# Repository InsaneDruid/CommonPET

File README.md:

# The CommonPET
The CommonPET is a 100% compatible replica of the SuperPet combo board for PET/CBM 8032 computers from 1981.
It implements all the features, including the 64K RAM addon, compatibility for the OS9 MMU well as the support for the internal RS-232 connector.

Most of the components are readily available. Chips not available from Mouser or Digikey can still be purchased as NOS from a variety of sources.

[Schematic](https://github.com/InsaneDruid/CommonPET/blob/main/CommonPET.pdf "Schematic")  

[Bill of Materials](https://htmlpreview.github.io/?https://github.com/InsaneDruid/CommonPET/blob/main/bom/CommonPET_bom.html "Bill of Materials")
## The Firmware
The Firmware of the SuperPET is available at zimmers.net: http://www.zimmers.net/anonftp/pub/cbm/firmware/computers/pet/SuperPET/index.html

UA3: characters.901640-01.bin (PETside CharROM):

U47: waterloo-a000-bfff.970018-12.bin

U48: waterloo-c000-dfff.970019-12.bin

U49: waterloo-e000-ffff-970034-12.bin (50Hz Version)

U49: waterloo-e000-ffff.970020-12.bin (60Hz Version)

Adapters to use 2764 EPROM work, 27hc641 that are programmed to be pin compatible to 2364 are recommended.

## The RS232 interface
CBM in its infinite wisdom only provided +5V and -9V for the 1488 line driver. A low voltage 1488E or 14C88 is recommended.

## The OS/9 MMU addon board
A replica of the OS/9 addon board can be found in the [os9_mmu folder](https://github.com/InsaneDruid/CommonPET/blob/main/os9_mmu/ "os9_mmu folder")

## The License
This work is licensed under a Creative Commons Attribution-ShareAlike 4.0 International License.  
See https://creativecommons.org/licenses/by-sa/4.0/.

## The Credits
This work would not have been possible without the help from a bunch of amazing people from [VzEkC e. V. forums](https://forum.classic-computing.de/forum/ "forum.classic-computing.de"). Many thanks go out to:

* *for(;;)* - for creating the amazing µMMF project that inspired this work
* *vossi* - for providing excellent images of a ASSY 324100 board
* *CBM_Ba* and *Richi*- for building and testing the first prototype

Special credits go out to *Mike Naberezny* for researching the OS/9 MMU schematics

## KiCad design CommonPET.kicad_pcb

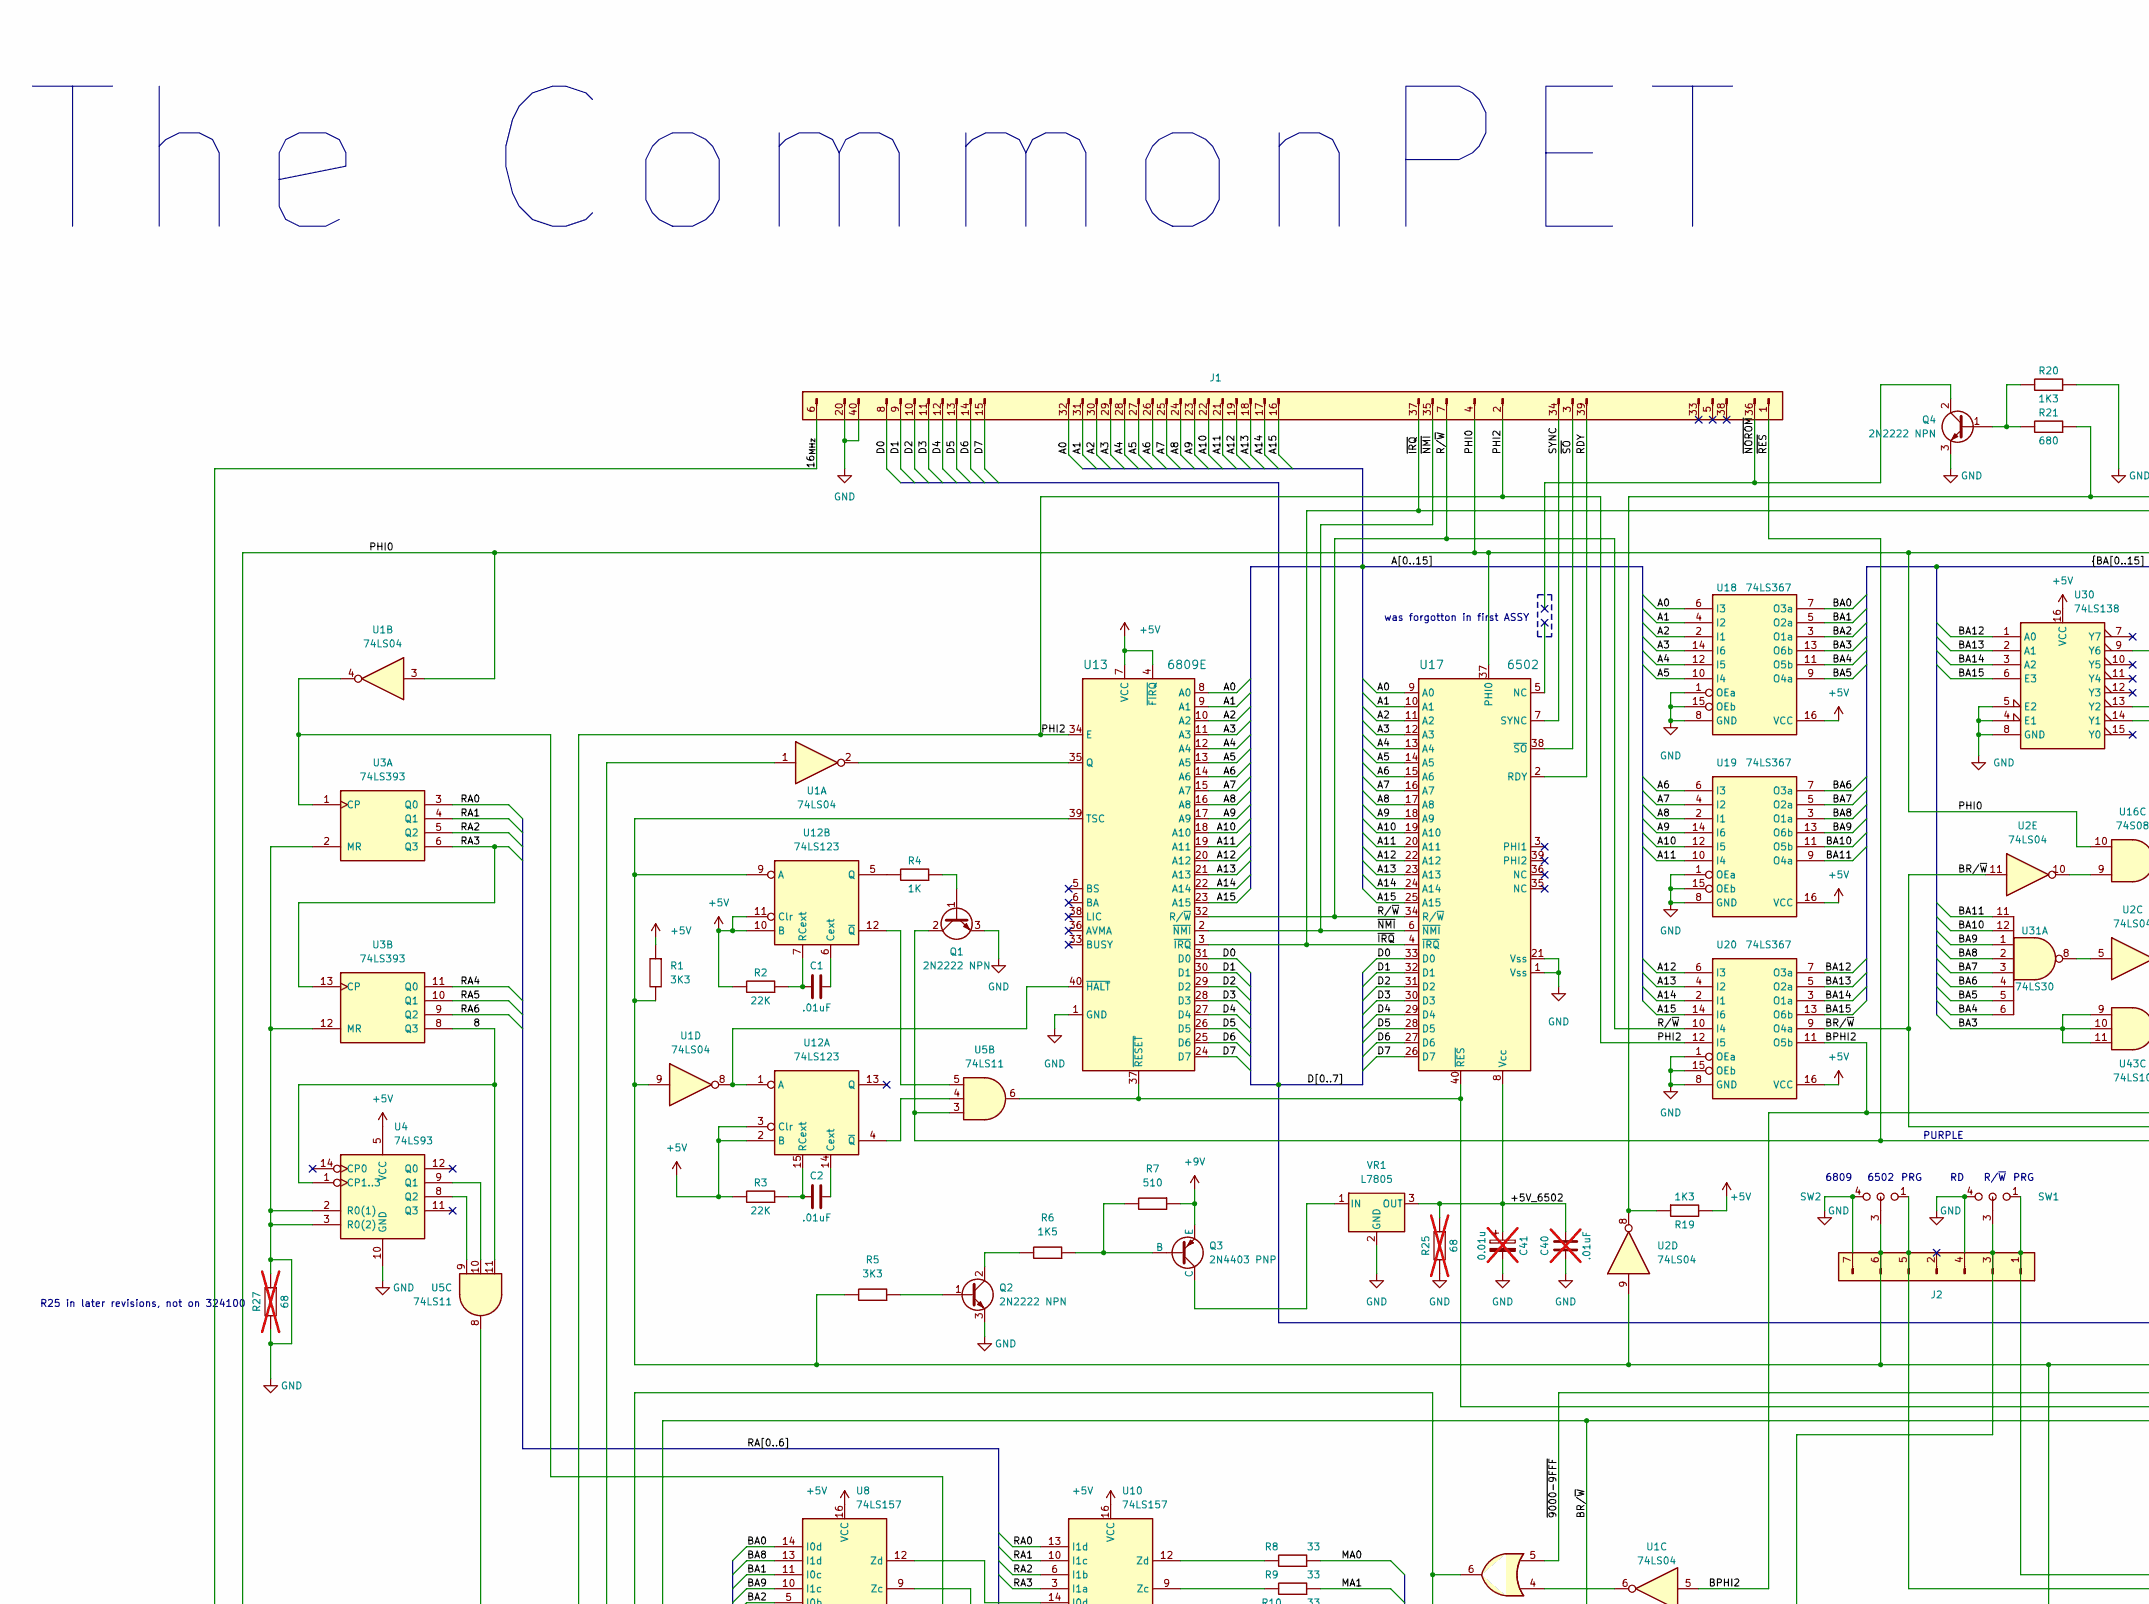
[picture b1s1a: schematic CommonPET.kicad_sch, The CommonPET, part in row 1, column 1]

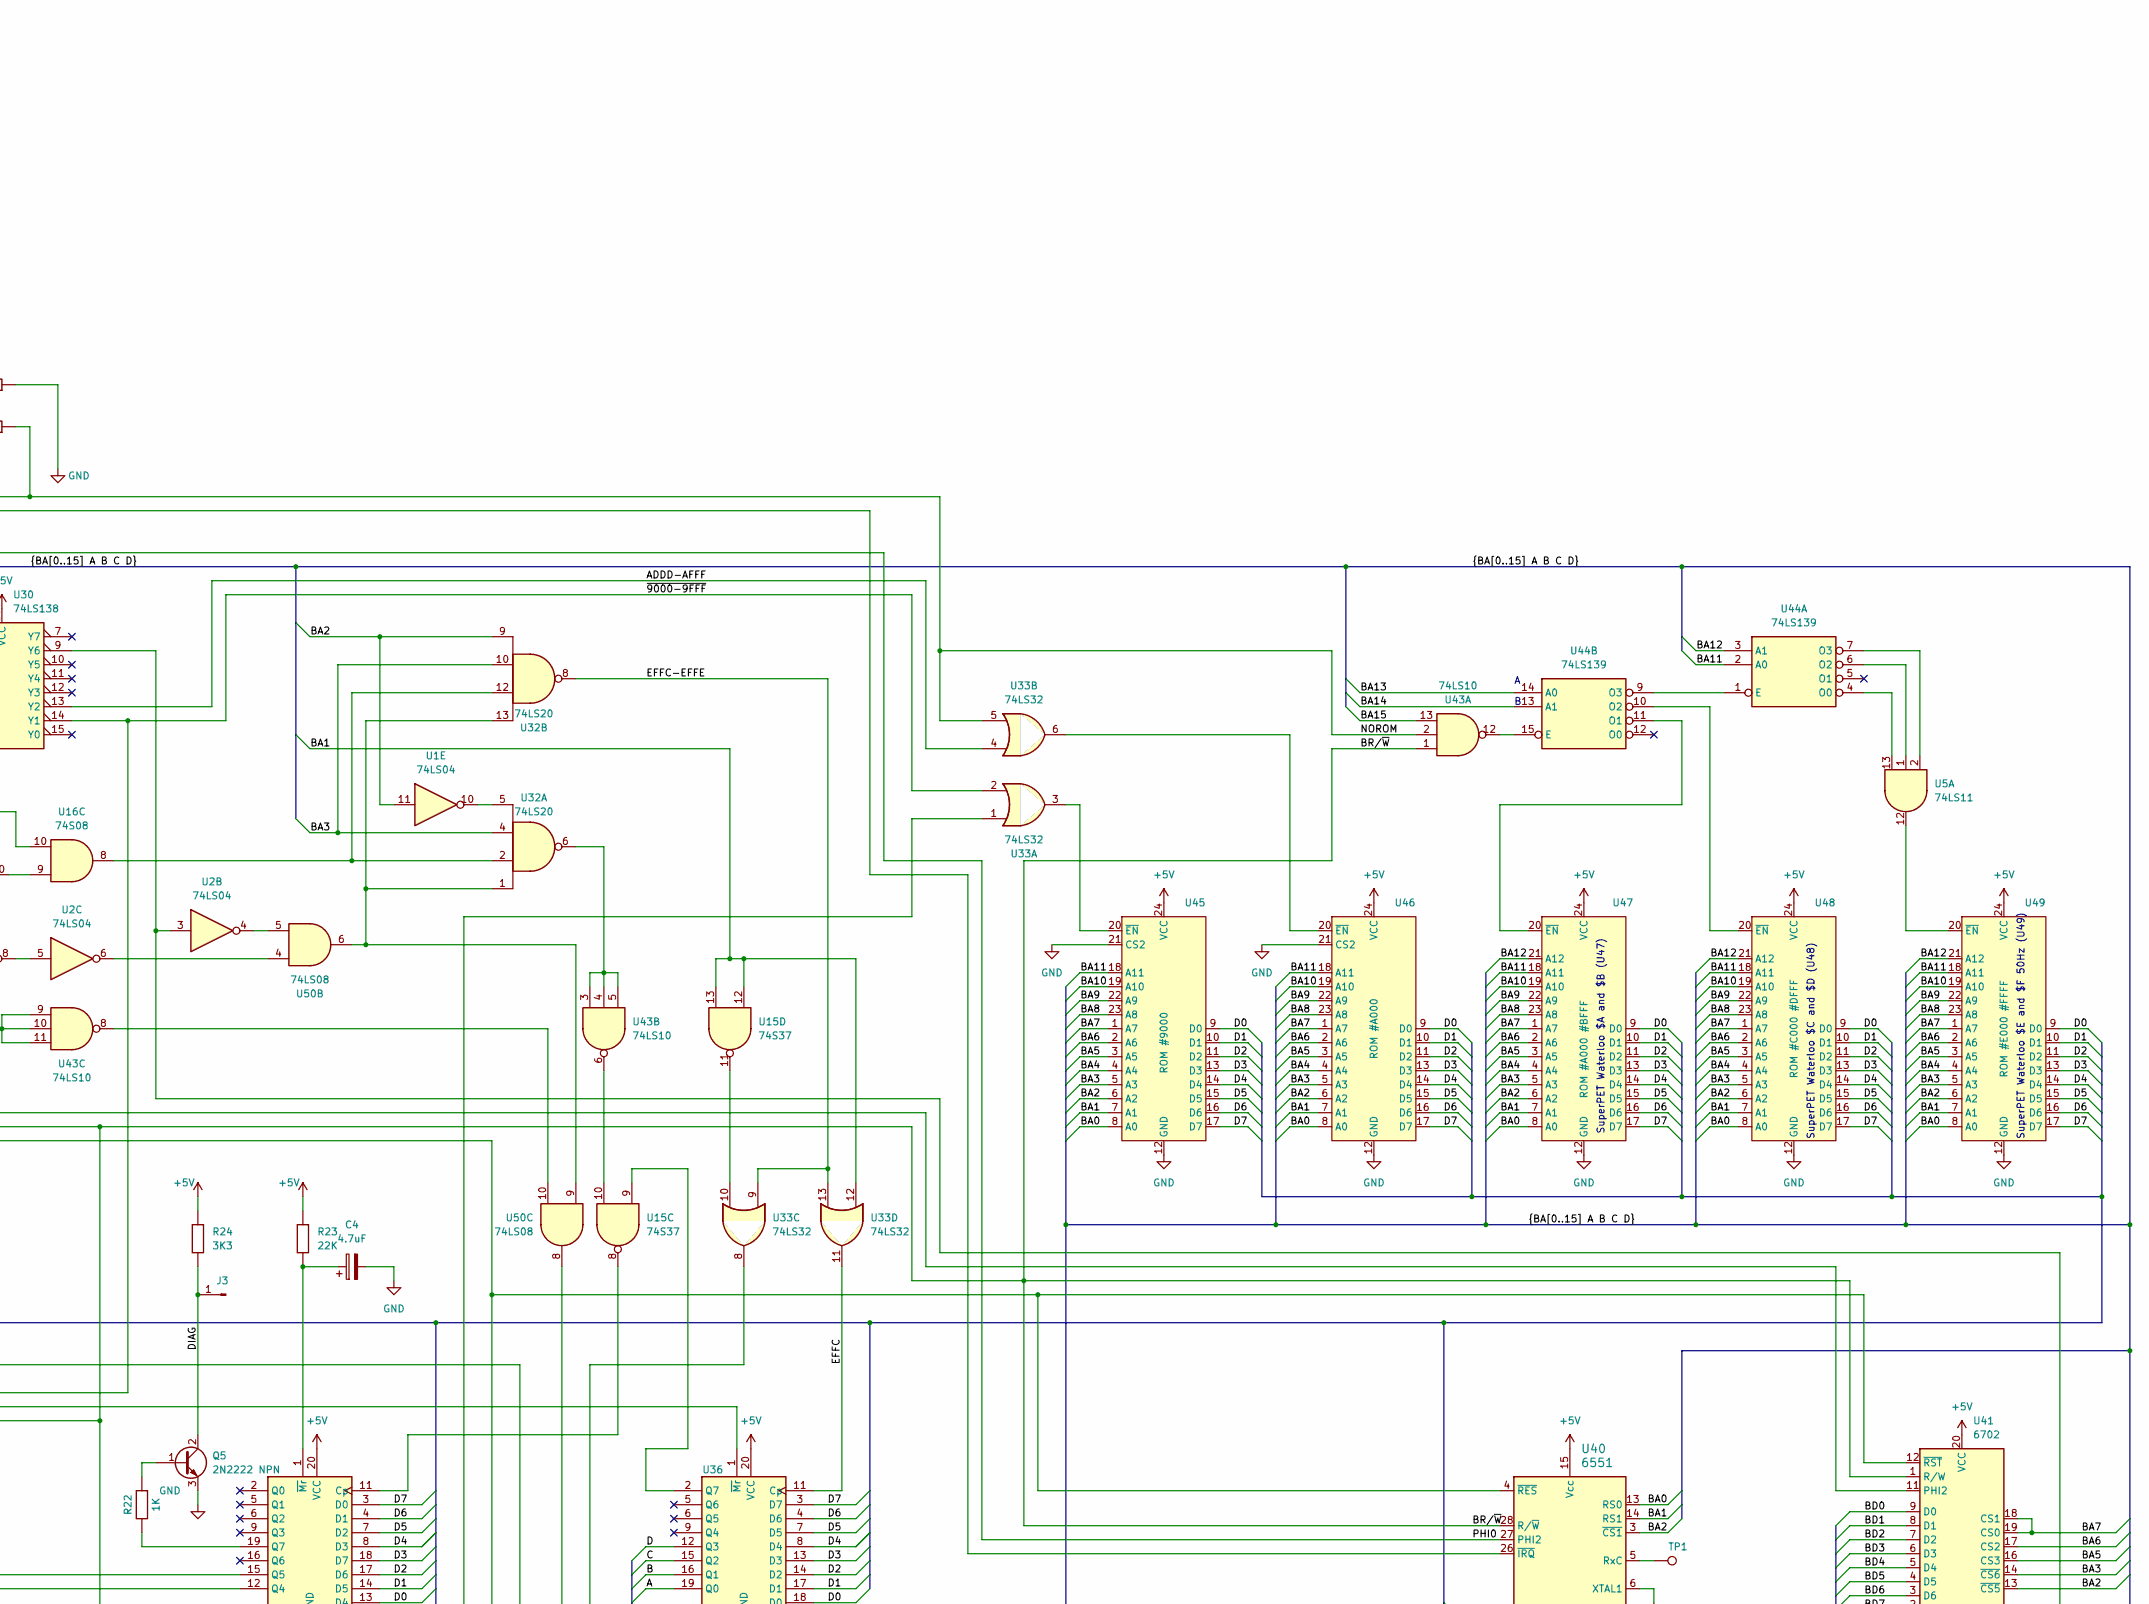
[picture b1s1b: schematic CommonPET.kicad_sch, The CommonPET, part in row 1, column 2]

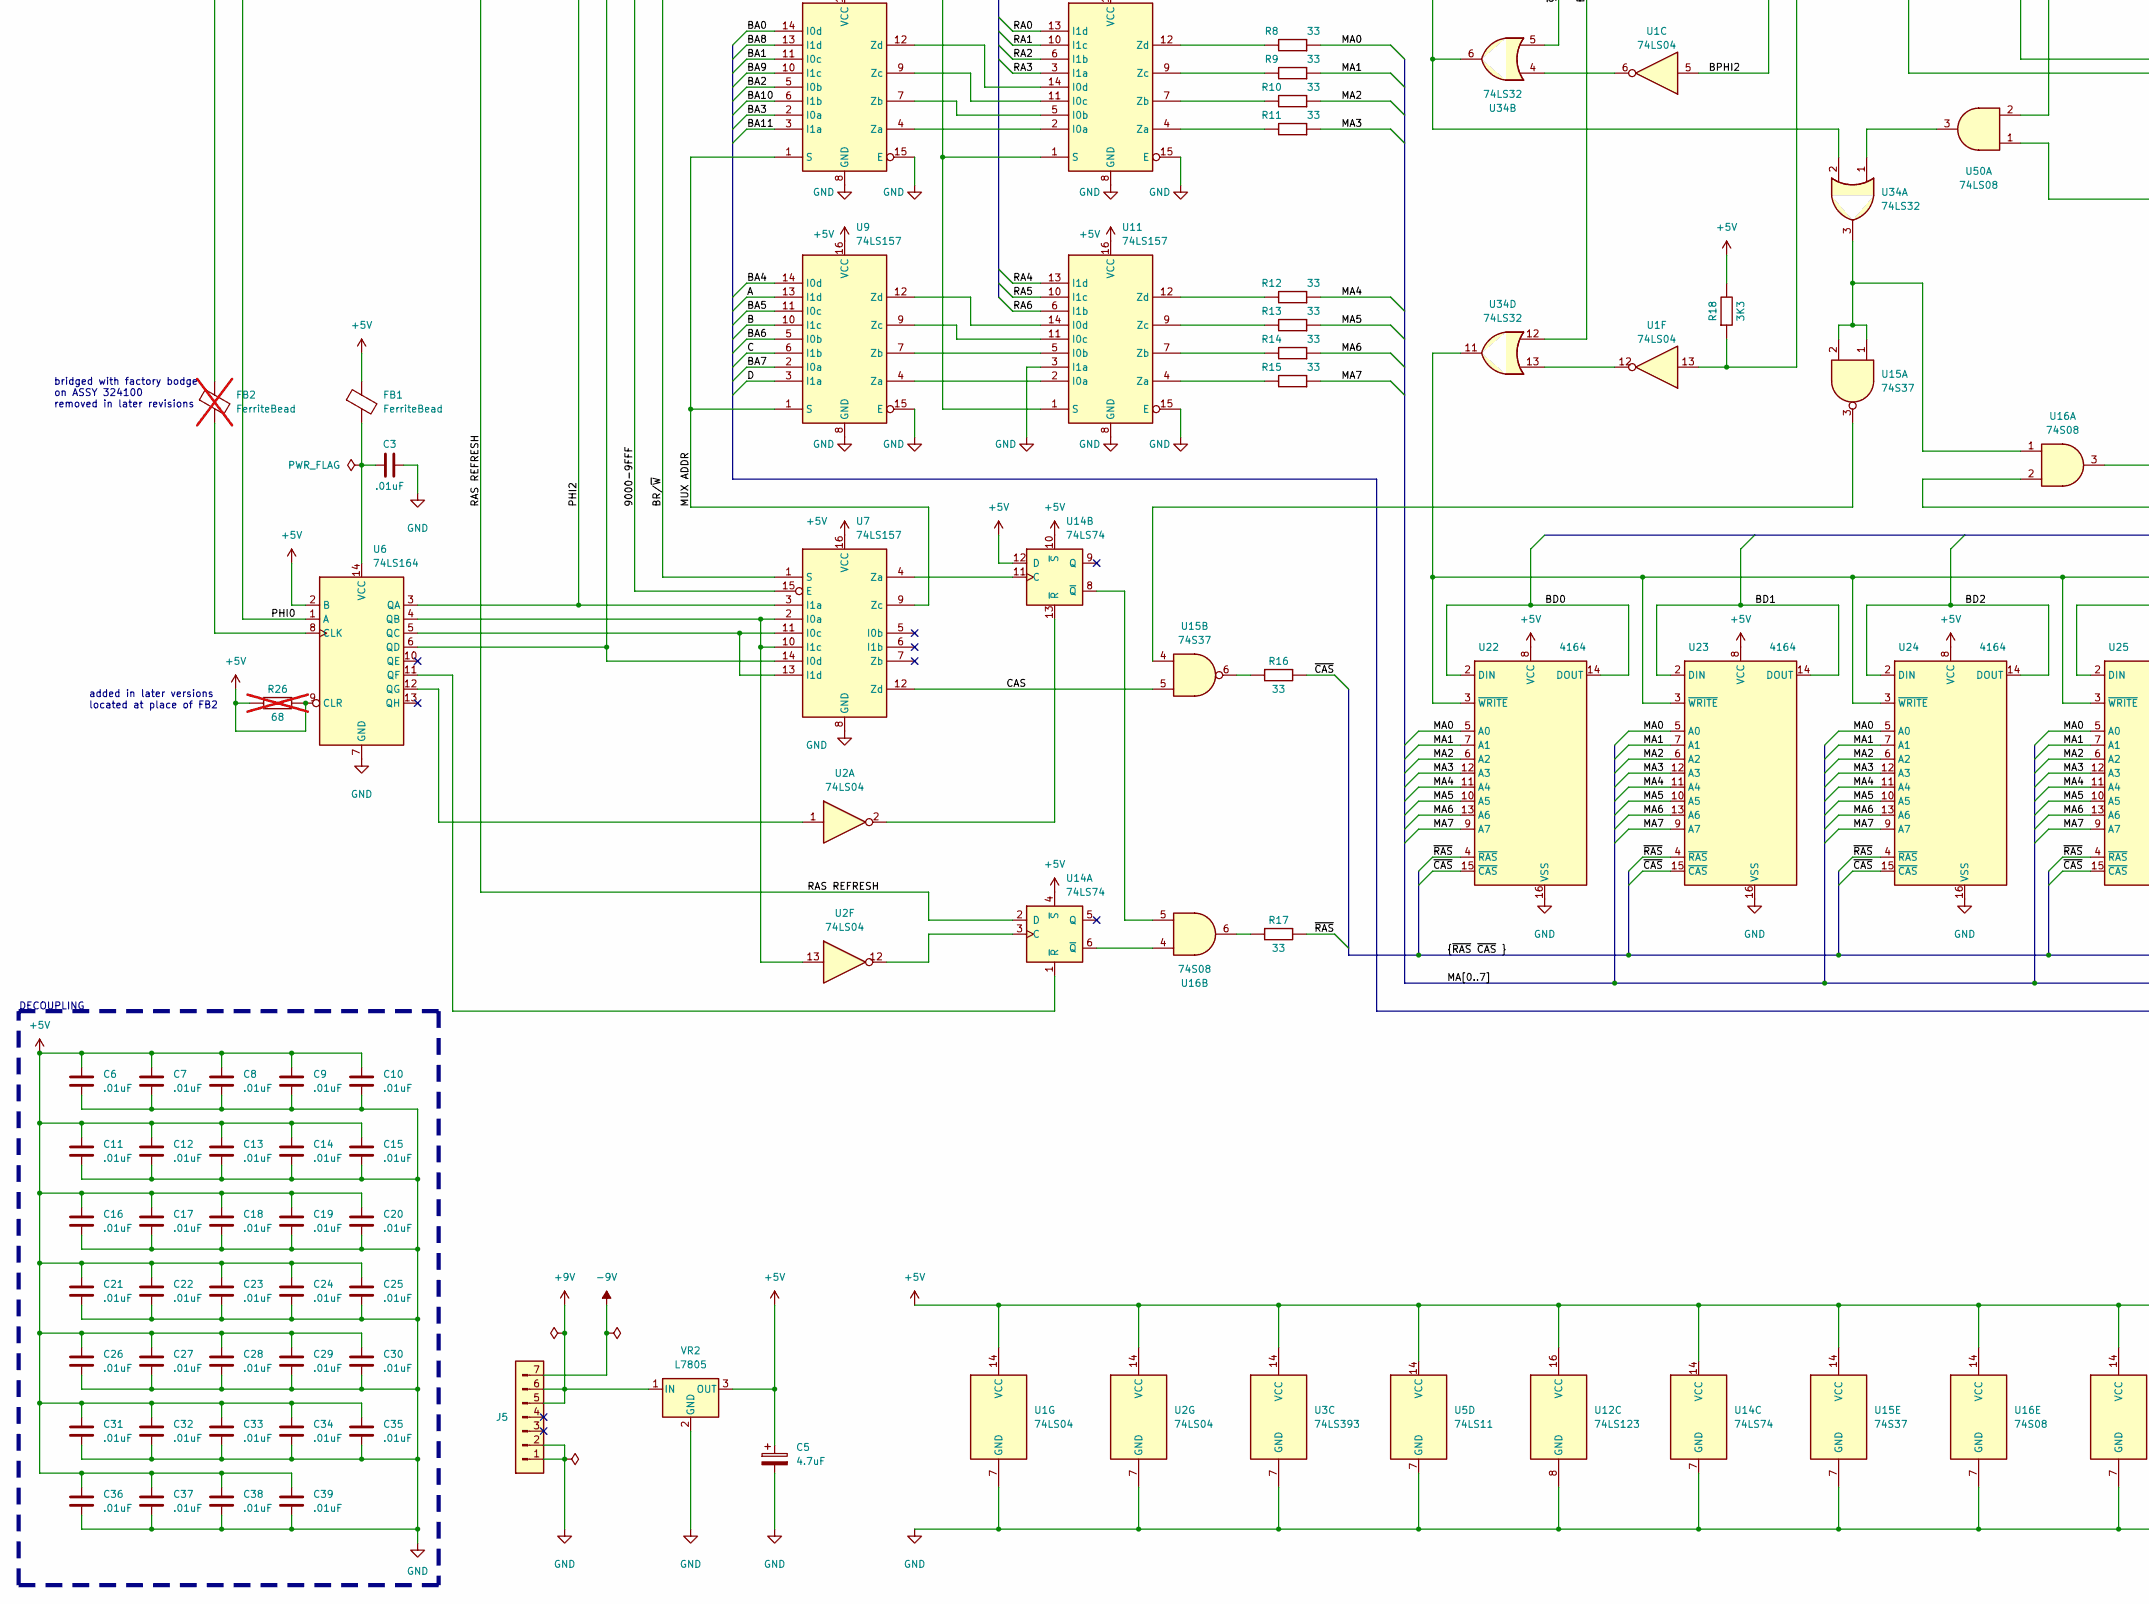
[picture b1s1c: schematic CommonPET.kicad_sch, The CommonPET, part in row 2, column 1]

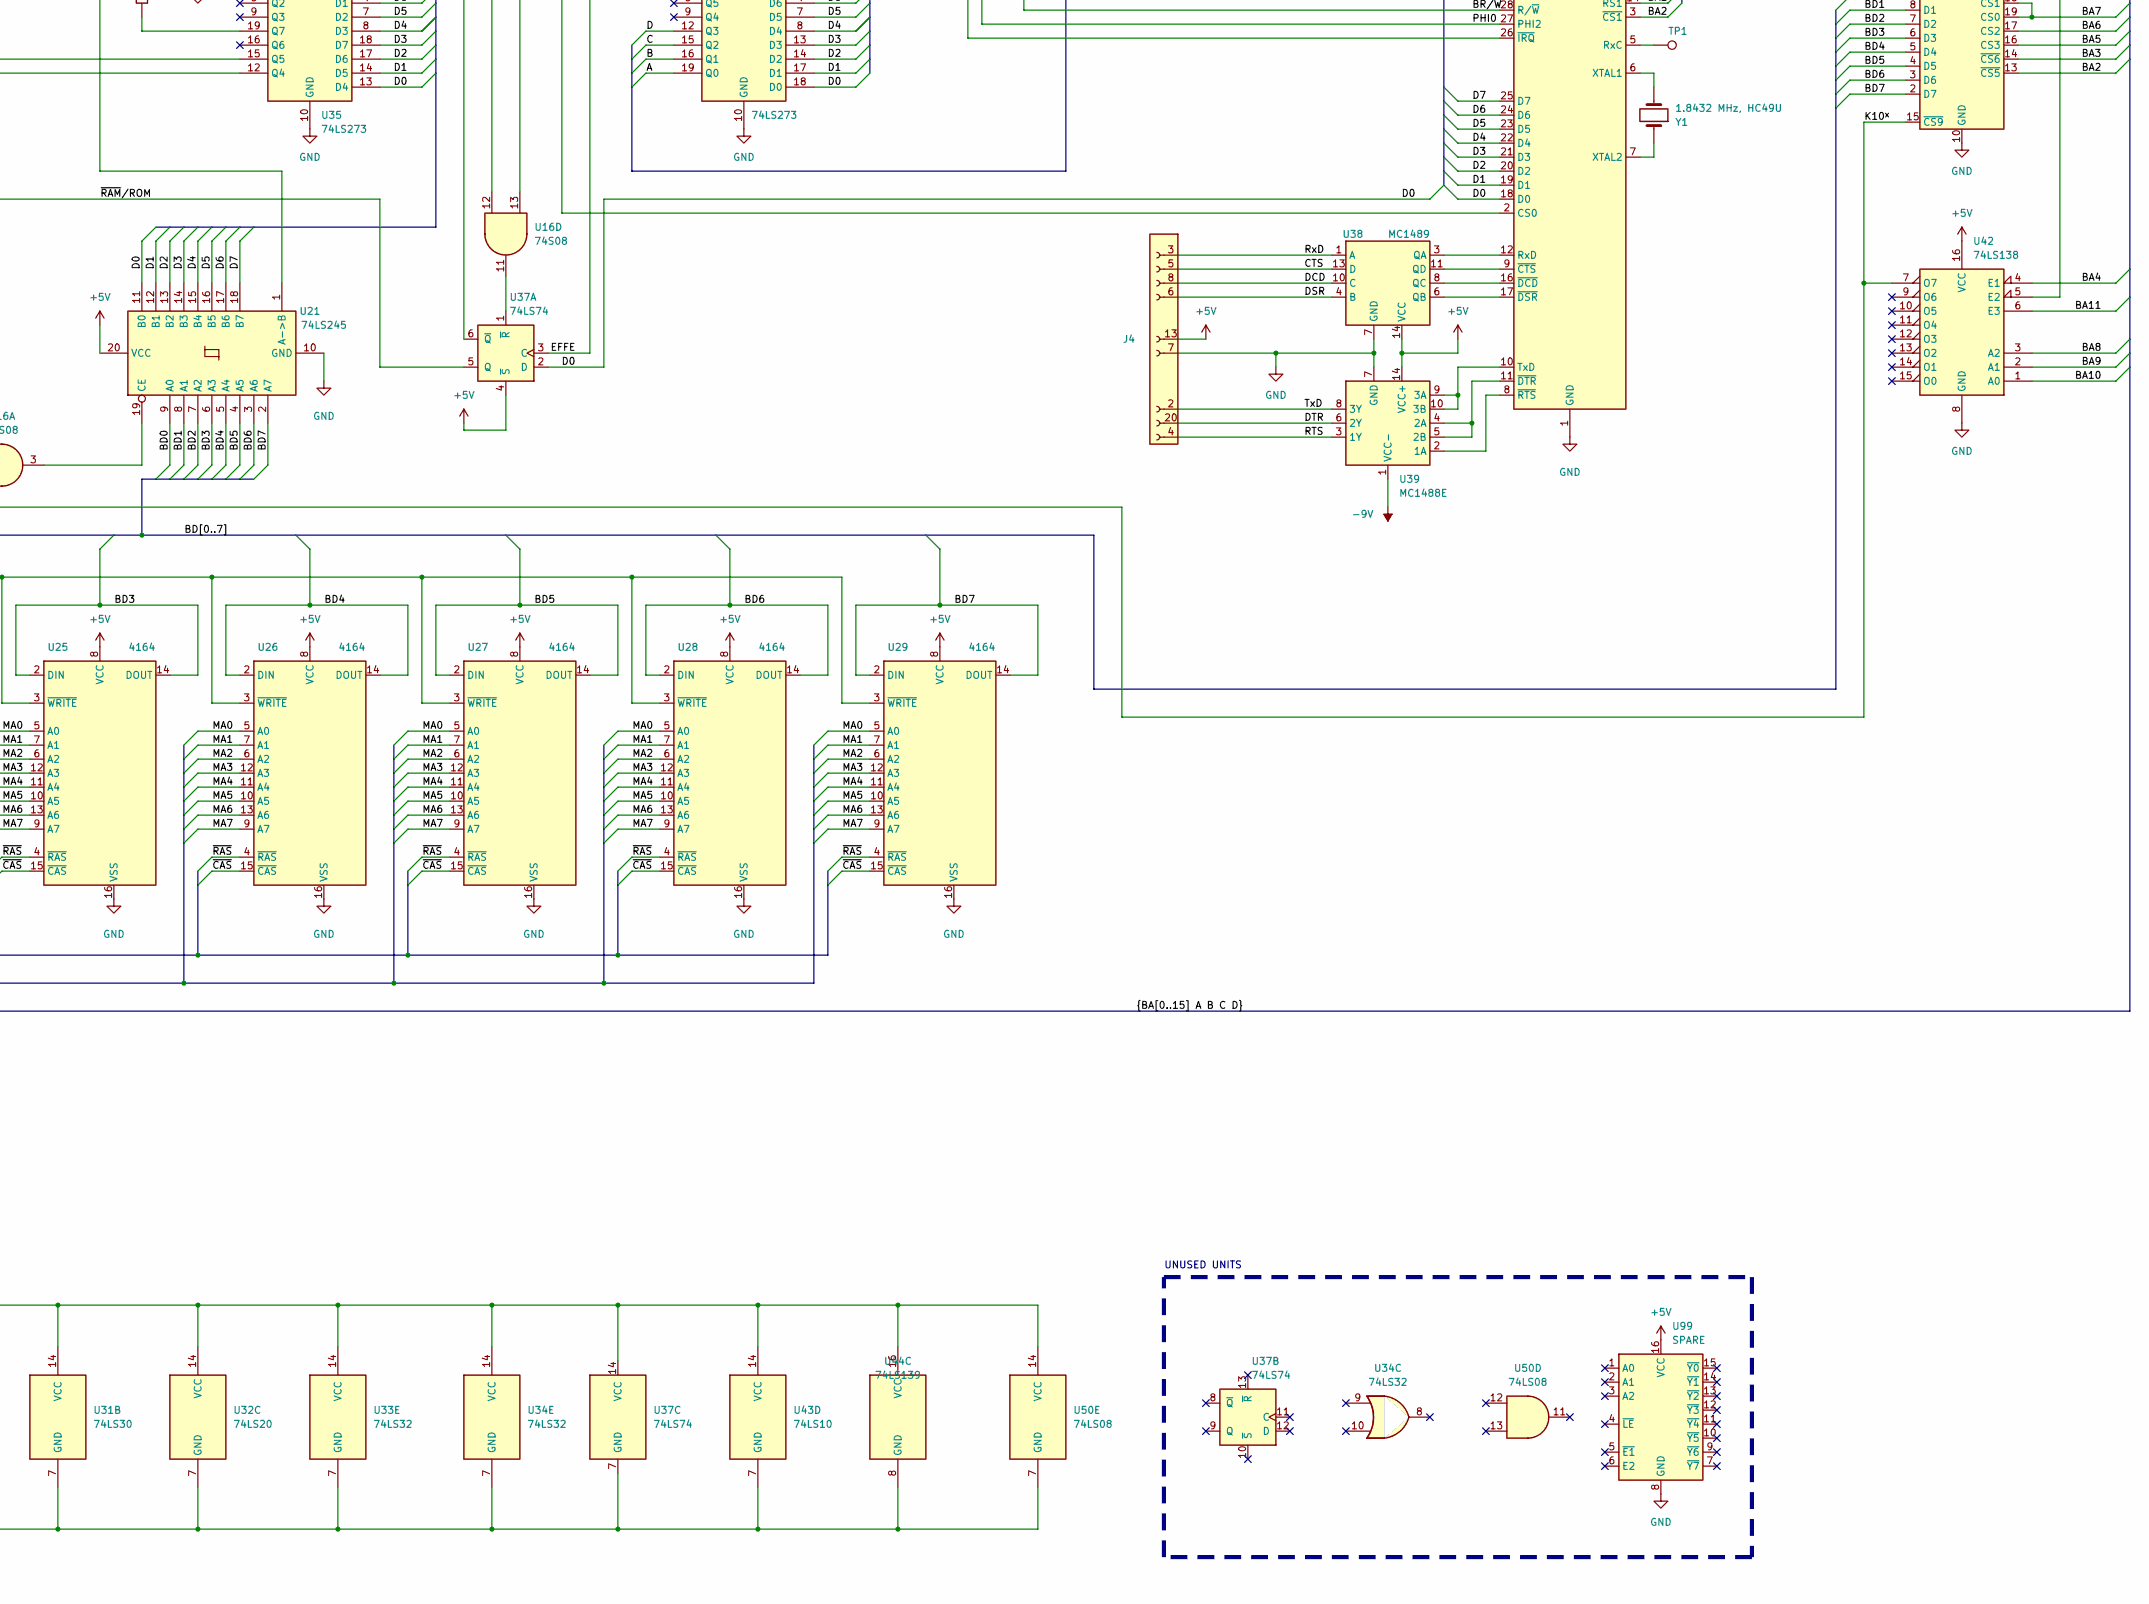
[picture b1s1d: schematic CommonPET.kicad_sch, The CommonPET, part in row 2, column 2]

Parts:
C1, C2, C3, C6, C7, C8, C9, C10, C11, C12, C13, C14, C15, C16, C17, C18, C19, C20, C21, C22, C23, C24, C25, C26, C27, C28, C29, C30, C31, C32, C33, C34, C35, C36, C37, C38, C39: .01uF; C_Axial_L3.8mm_D2.6mm_P12.54mm_Horizontal
C4, C5: 4.7uF; CP_Axial_L11.0mm_D6.0mm_P20.32mm
C40: .01uF; C_Axial_L3.8mm_D2.6mm_P12.54mm_Horizontal_notpopulated; not fitted
C41: 0.01u; CP_Axial_L11.0mm_D6.0mm_P20.32mm_notpopulated; not fitted
FB1: FerriteBead; C_Axial_L3.8mm_D2.6mm_P12.54mm_Horizontal
FB2: FerriteBead; C_Axial_L3.8mm_D2.6mm_P12.54mm_Horizontal; not fitted
J1: Conn_01x40_Pin; PinHeader_2x20_P2.54mm_Vertical
J2, J5: Conn_01x07_Pin; PinHeader_1x07_P2.54mm_Vertical
J3: Conn_01x01_Pin; PinHeader_1x01_P2.54mm_Vertical
J4: Conn_01x25_Socket; DSUB-25_Female_Horizontal_P2.77x2.84mm_EdgePinOffset9.90mm_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
Q1, Q2, Q4, Q5: 2N2222 NPN; TO-18-3
Q3: 2N4403 PNP; TO-92
R1, R5, R18, R24: 3K3; R_Axial_DIN0207_L6.3mm_D2.5mm_P15.24mm_Horizontal
R2, R3, R23: 22K; R_Axial_DIN0207_L6.3mm_D2.5mm_P15.24mm_Horizontal
R4, R22: 1K; R_Axial_DIN0207_L6.3mm_D2.5mm_P15.24mm_Horizontal
R6: 1K5; R_Axial_DIN0207_L6.3mm_D2.5mm_P15.24mm_Horizontal
R7: 510; R_Axial_DIN0207_L6.3mm_D2.5mm_P15.24mm_Horizontal
R8, R9, R10, R11, R12, R13, R14, R15, R16, R17: 33; R_Axial_DIN0207_L6.3mm_D2.5mm_P15.24mm_Horizontal
R19, R20: 1K3; R_Axial_DIN0207_L6.3mm_D2.5mm_P15.24mm_Horizontal
R21: 680; R_Axial_DIN0207_L6.3mm_D2.5mm_P15.24mm_Horizontal
R25: 68; R_Axial_DIN0207_L6.3mm_D2.5mm_P15.24mm_Horizontal__notpopul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; not fitted
R26, R27: 68; R_Axial_DIN0207_L6.3mm_D2.5mm_P15.24mm_Horizontal; not fitted
SW1, SW2: SW_DP3T
TP1: TestPoint; TestPoint_THTPad_1.0x1.0mm_Drill0.5mm
U1, U2: 74LS04; DIP-14_W7.62mm
U3: 74LS393; DIP-14_W7.62mm
U4: 74LS93; DIP-14_W7.62mm
U5: 74LS11; DIP-14_W7.62mm
U6: 74LS164; DIP-14_W7.62mm
U7, U8, U9, U10, U11: 74LS157; DIP-16_W7.62mm
U12: 74LS123; DIP-16_W7.62mm
U13: 6809E; DIP-40_W15.24mm_socket
U14, U37: 74LS74; DIP-14_W7.62mm
U15: 74S37; DIP-14_W7.62mm
U16: 74S08; DIP-14_W7.62mm
U17: 6502; DIP-40_W15.24mm_socket
U18, U19, U20: 74LS367; DIP-16_W7.62mm
U21: 74LS245; DIP-20_W7.62mm
U22, U23, U24, U25, U26, U27, U28, U29: 4164; DIP-16_W7.62mm
U30, U42: 74LS138; DIP-16_W7.62mm
U31: 74LS30; DIP-14_W7.62mm
U32: 74LS20; DIP-14_W7.62mm
U33, U34: 74LS32; DIP-14_W7.62mm
U35, U36: 74LS273; DIP-20_W7.62mm
U38: MC1489; DIP-14_W7.62mm
U39: MC1488E; DIP-14_W7.62mm
U40: 6551; DIP-28_W15.24mm
U41: 6702; DIP-20_W7.62mm
U43: 74LS10; DIP-14_W7.62mm
U44: 74LS139; DIP-16_W7.62mm
U45: ROM #9000; DIP-24_W15.24mm_socket
U46: ROM #A000; DIP-24_W15.24mm_socket
U47: ROM #A000 #BFFF; DIP-24_W15.24mm
U48: ROM #C000 #DFFF; DIP-24_W15.24mm
U49: ROM #E000 #FFFF; DIP-24_W15.24mm
U50: 74LS08; DIP-14_W7.62mm
U99: SPARE; SPARE_DIP-16_W7.62mm
VR1: L7805; TO-220-3_Horizontal_TabDown
VR2: L7805; TO-220-3_Horizontal_TabDown_HeatSinked
Y1: 1.8432 MHz, HC49U; Crystal_HC33-U_Horizontal

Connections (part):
+5V: C5.1, C6.1, C7.1, C8.1, C9.1, C10.1, C11.1, C12.2, C13.2, C14.1, C15.1, C16.1, C17.1, C18.1, C19.1, C20.1, C21.1, C22.1, C23.1, C24.1, C25.1, C26.1, C27.1, C28.1, C29.1, C30.1, C31.1, C32.1, C33.1, C34.1, C35.1, C36.1, C37.1, C38.1, C39.1, FB1.1, J4.13 (Pin_7), R1.2, R2.1, R3.1, R18.1, R19.1, R23.2, R24.2, U1.14 (VCC), U2.14 (VCC), U3.14 (VCC), U4.5 (VCC), U5.14 (VCC), U6.2 (B), U6.9 (CLR), U7.16 (VCC), U8.16 (VCC), U9.16 (VCC), U10.16 (VCC), U11.16 (VCC), U12.2 (B), U12.3 (Clr), U12.10 (B), U12.11 (Clr), U12.16 (VCC), U13.4 (~FIRQ), U13.7 (VCC), U14.4 (~S), U14.10 (~S), U14.12 (D), U14.14 (VCC), U15.14 (VCC), U16.14 (VCC), U18.16 (VCC), U19.16 (VCC), U20.16 (VCC), U21.20 (VCC), U22.8 (VCC), U23.8 (VCC), U24.8 (VCC), U25.8 (VCC), U26.8 (VCC), U27.8 (VCC), U28.8 (VCC)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
+9V: J5.5, J5.6, Q3.3 (E), R7.2, VR2.1 (IN)
-9V: J5.7, U39.1 (VCC-)
/8: U3.8 (Q3), U4.1 (CP1..3), U5.11
/16_{MHz}: FB2.1, J1.6
/9000-9FFF: U7.15 (E), U34.2, U34.6
/+5V_6502: C40.2, C41.1, R25.2, U17.8 (Vcc), VR1.3 (OUT)
/A: U9.13 (I1d), U36.19 (Q0)
/A0: J1.32, U13.8 (A0), U17.9 (A0), U18.6 (I3)
/A1: J1.31, U13.9 (A1), U17.10 (A1), U18.4 (I2)
/A2: J1.30, U13.10 (A2), U17.11 (A2), U18.2 (I1)
/A3: J1.29, U13.11 (A3), U17.12 (A3), U18.14 (I6)
/A4: J1.28, U13.12 (A4), U17.13 (A4), U18.12 (I5)
/A5: J1.27, U13.13 (A5), U17.14 (A5), U18.10 (I4)
/A6: J1.26, U13.14 (A6), U17.15 (A6), U19.6 (I3)
/A7: J1.25, U13.15 (A7), U17.16 (A7), U19.4 (I2)
/A8: J1.24, U13.16 (A8), U17.17 (A8), U19.2 (I1)
/A9: J1.23, U13.17 (A9), U17.18 (A9), U19.14 (I6)
/A10: J1.22, U13.18 (A10), U17.19 (A10), U19.12 (I5)
/A11: J1.21, U13.19 (A11), U17.20 (A11), U19.10 (I4)
/A12: J1.19, U13.20 (A12), U17.22 (A12), U20.6 (I3)
/A13: J1.18, U13.21 (A13), U17.23 (A13), U20.4 (I2)
/A14: J1.17, U13.22 (A14), U17.24 (A14), U20.2 (I1)
/A15: J1.16, U13.23 (A15), U17.25 (A15), U20.14 (I6)
/ADDD-AFFF: U30.13 (Y2), U33.4
/B: U9.10 (I1c), U36.16 (Q1)
/BA0: U8.14 (I0d), U18.7 (O3a), U40.13 (RS0), U45.8 (A0), U46.8 (A0), U47.8 (A0), U48.8 (A0), U49.8 (A0)
/BA1: U8.11 (I0c), U15.12, U15.13, U18.5 (O2a), U33.12, U40.14 (RS1), U45.7 (A1), U46.7 (A1), U47.7 (A1), U48.7 (A1), U49.7 (A1)
/BA2: U1.11, U8.5 (I0b), U18.3 (O1a), U32.9, U40.3 (~CS1), U41.13 (~CS5), U45.6 (A2), U46.6 (A2), U47.6 (A2), U48.6 (A2), U49.6 (A2)
/BA3: U8.2 (I0a), U18.13 (O6b), U32.4, U32.10, U41.14 (~CS6), U43.9, U43.10, U43.11, U45.5 (A3), U46.5 (A3), U47.5 (A3), U48.5 (A3), U49.5 (A3)
/BA4: U9.14 (I0d), U18.11 (O5b), U31.6, U42.4 (E1), U45.4 (A4), U46.4 (A4), U47.4 (A4), U48.4 (A4), U49.4 (A4)
/BA5: U9.11 (I0c), U18.9 (O4a), U31.5, U41.16 (CS3), U45.3 (A5), U46.3 (A5), U47.3 (A5), U48.3 (A5), U49.3 (A5)
/BA6: U9.5 (I0b), U19.7 (O3a), U31.4, U41.17 (CS2), U45.2 (A6), U46.2 (A6), U47.2 (A6), U48.2 (A6), U49.2 (A6)
/BA7: U9.2 (I0a), U19.5 (O2a), U31.3, U41.18 (CS1), U41.19 (CS0), U45.1 (A7), U46.1 (A7), U47.1 (A7), U48.1 (A7), U49.1 (A7)
/BA8: U8.13 (I1d), U19.3 (O1a), U31.2, U42.3 (A2), U45.23 (A8), U46.23 (A8), U47.23 (A8), U48.23 (A8), U49.23 (A8)
/BA9: U8.10 (I1c), U19.13 (O6b), U31.1, U42.2 (A1), U45.22 (A9), U46.22 (A9), U47.22 (A9), U48.22 (A9), U49.22 (A9)
/BA10: U8.6 (I1b), U19.11 (O5b), U31.12, U42.1 (A0), U45.19 (A10), U46.19 (A10), U47.19 (A10), U48.19 (A10), U49.19 (A10)
/BA11: U8.3 (I1a), U19.9 (O4a), U31.11, U42.6 (E3), U44.2 (A0), U45.18 (A11), U46.18 (A11), U47.18 (A11), U48.18 (A11), U49.18 (A11)
/BA12: U20.7 (O3a), U30.1 (A0), U44.3 (A1), U47.21 (A12), U48.21 (A12), U49.21 (A12)
/BA13: U20.5 (O2a), U30.2 (A1), U44.14 (A0)
/BA14: U20.3 (O1a), U30.3 (A2), U44.13 (A1)
/BA15: U20.13 (O6b), U30.6 (E3), U43.13
/BD0: U21.9 (A0), U22.2 (DIN), U22.14 (DOUT), U41.9 (D0)
/BD1: U21.8 (A1), U23.2 (DIN), U23.14 (DOUT), U41.8 (D1)
/BD2: U21.7 (A2), U24.2 (DIN), U24.14 (DOUT), U41.7 (D2)
/BD3: U21.6 (A3), U25.2 (DIN), U25.14 (DOUT), U41.6 (D3)
/BD4: U21.5 (A4), U26.2 (DIN), U26.14 (DOUT), U41.5 (D4)
/BD5: U21.4 (A5), U27.2 (DIN), U27.14 (DOUT), U41.4 (D5)
/BD6: U21.3 (A6), U28.2 (DIN), U28.14 (DOUT), U41.3 (D6)
/BD7: U21.2 (A7), U29.2 (DIN), U29.14 (DOUT), U41.2 (D7)
/BPHI2: U1.5, U20.11 (O5b), U41.11 (PHI2)
/BR/~W: U2.11, U7.1 (S), U20.9 (O4a), U21.1 (A->B), U34.12, U40.28 (R/~W), U41.1 (R/W), U43.1
/C: U9.6 (I1b), U36.15 (Q2)
/CAS: U7.12 (Zd), U15.5
/CTS: J4.5, U38.13 (D)
/D: U9.3 (I1a), U36.12 (Q3)
/D0: J1.8, U13.31 (D0), U17.33 (D0), U21.11 (B0), U35.13 (D4), U36.18 (D0), U37.2 (D), U40.18 (D0), U45.9 (D0), U46.9 (D0), U47.9 (D0), U48.9 (D0), U49.9 (D0)
/D1: J1.9, U13.30 (D1), U17.32 (D1), U21.12 (B1), U35.14 (D5), U36.17 (D1), U40.19 (D1), U45.10 (D1), U46.10 (D1), U47.10 (D1), U48.10 (D1), U49.10 (D1)
/D2: J1.10, U13.29 (D2), U17.31 (D2), U21.13 (B2), U35.17 (D6), U36.14 (D2), U40.20 (D2), U45.11 (D2), U46.11 (D2), U47.11 (D2), U48.11 (D2), U49.11 (D2)
/D3: J1.11, U13.28 (D3), U17.30 (D3), U21.14 (B3), U35.18 (D7), U36.13 (D3), U40.21 (D3), U45.13 (D3), U46.13 (D3), U47.13 (D3), U48.13 (D3), U49.13 (D3)
/D4: J1.12, U13.27 (D4), U17.29 (D4), U21.15 (B4), U35.8 (D3), U36.8 (D4), U40.22 (D4), U45.14 (D4), U46.14 (D4), U47.14 (D4), U48.14 (D4), U49.14 (D4)
/D5: J1.13, U13.26 (D5), U17.28 (D5), U21.16 (B5), U35.7 (D2), U36.7 (D5), U40.23 (D5), U45.15 (D5), U46.15 (D5), U47.15 (D5), U48.15 (D5), U49.15 (D5)
/D6: J1.14, U13.25 (D6), U17.27 (D6), U21.17 (B6), U35.4 (D1), U36.4 (D6), U40.24 (D6), U45.16 (D6), U46.16 (D6), U47.16 (D6), U48.16 (D6), U49.16 (D6)
/D7: J1.15, U13.24 (D7), U17.26 (D7), U21.18 (B7), U35.3 (D0), U36.3 (D7), U40.25 (D7), U45.17 (D7), U46.17 (D7), U47.17 (D7), U48.17 (D7), U49.17 (D7)
/DCD: J4.8, U38.10 (C)
/DIAG: J3.1, Q5.2 (C), R24.1
/DSR: J4.6, U38.4 (B)
/DTR: J4.20, U39.6 (2Y)
/EFFC: U33.11, U36.11 (Cp)
/EFFC-EFFE: U32.8, U33.9, U33.13
/EFFE: U33.8, U37.3 (C)
/K10^{x}: U16.2, U41.15 (~CS9), U42.7 (O7)
/MA0: R8.2, U22.5 (A0), U23.5 (A0), U24.5 (A0), U25.5 (A0), U26.5 (A0), U27.5 (A0), U28.5 (A0), U29.5 (A0)
/MA1: R9.2, U22.7 (A1), U23.7 (A1), U24.7 (A1), U25.7 (A1), U26.7 (A1), U27.7 (A1), U28.7 (A1), U29.7 (A1)
/MA2: R10.2, U22.6 (A2), U23.6 (A2), U24.6 (A2), U25.6 (A2), U26.6 (A2), U27.6 (A2), U28.6 (A2), U29.6 (A2)
/MA3: R11.2, U22.12 (A3), U23.12 (A3), U24.12 (A3), U25.12 (A3), U26.12 (A3), U27.12 (A3), U28.12 (A3), U29.12 (A3)
/MA4: R12.2, U22.11 (A4), U23.11 (A4), U24.11 (A4), U25.11 (A4), U26.11 (A4), U27.11 (A4), U28.11 (A4), U29.11 (A4)
/MA5: R13.2, U22.10 (A5), U23.10 (A5), U24.10 (A5), U25.10 (A5), U26.10 (A5), U27.10 (A5), U28.10 (A5), U29.10 (A5)
/MA6: R14.2, U22.13 (A6), U23.13 (A6), U24.13 (A6), U25.13 (A6), U26.13 (A6), U27.13 (A6), U28.13 (A6), U29.13 (A6)
/MA7: R15.2, U22.9 (A7), U23.9 (A7), U24.9 (A7), U25.9 (A7), U26.9 (A7), U27.9 (A7), U28.9 (A7), U29.9 (A7)
/MUX ADDR: U7.9 (Zc), U8.1 (S), U9.1 (S)
/NOROM: R19.2, R21.2, U2.8, U33.5, U43.2
/PHI0: J1.4, U1.3, U6.1 (A), U16.10, U17.37 (PHI0), U40.27 (PHI2)
/PHI2: J1.2, U6.3 (QA), U7.3 (I1a), U13.34 (E), U20.12 (I5)
/RA0: U3.3 (Q0), U10.13 (I1d)
/RA1: U3.4 (Q1), U10.10 (I1c)
/RA2: U3.5 (Q2), U10.6 (I1b)
/RA3: U3.6 (Q3), U3.13 (CP), U10.3 (I1a)
/RA4: U3.11 (Q0), U11.13 (I1d)
/RA5: U3.10 (Q1), U11.10 (I1c)
/RA6: U3.9 (Q2), U11.6 (I1b)
/RAS REFRESH: U5.8, U14.2 (D)
/RDY: J1.39, U17.2 (RDY)
/RTS: J4.4, U39.3 (1Y)
/RxD: J4.3, U38.1 (A)
/R/~W: J1.7, U13.32 (R/~W), U17.34 (R/~W), U20.10 (I4)
/SYNC: J1.34, U17.7 (SYNC)
/TxD: J4.2, U39.8 (3Y)
/~9000-9FFF: U30.14 (Y1), U33.2, U34.5
/~CAS: R16.1, U22.15 (~CAS), U23.15 (~CAS), U24.15 (~CAS), U25.15 (~CAS), U26.15 (~CAS), U27.15 (~CAS), U28.15 (~CAS), U29.15 (~CAS)
/~IRQ: J1.37, U13.3 (~IRQ), U17.4 (~IRQ), U40.26 (~IRQ)
/~NMI: J1.35, U13.2 (~NMI), U17.6 (~NMI)
/~NOROM: J1.36, Q4.2 (C)
/~RAM/ROM: U37.5 (Q), U50.1
/~RAS: R17.1, U22.4 (~RAS), U23.4 (~RAS), U24.4 (~RAS), U25.4 (~RAS), U26.4 (~RAS), U27.4 (~RAS), U28.4 (~RAS), U29.4 (~RAS)
/~RES: J1.1, Q1.2 (C), U5.3, U16.12, U40.4 (~RES), U41.12 (~RST)
/~SO: J1.3, U17.38 (~SO)
GND: C3.2, C4.2, C5.2, C6.2, C7.2, C8.2, C9.2, C10.2, C11.2, C12.1, C13.1, C14.2, C15.2, C16.2, C17.2, C18.2, C19.2, C20.2, C21.2, C22.2, C23.2, C24.2, C25.2, C26.2, C27.2, C28.2, C29.2, C30.2, C31.2, C32.2, C33.2, C34.2, C35.2, C36.2, C37.2, C38.2, C39.2, C40.1, C41.2, J1.20, J1.40, J2.4, J2.7, J4.7, J5.1, J5.2, Q1.3 (E), Q2.3 (E), Q4.3 (E), Q5.3 (E), R20.2, R25.1, U1.7 (GND), U2.7 (GND), U3.2 (MR), U3.7 (GND), U3.12 (MR), U4.2 (R0(1)), U4.3 (R0(2)), U4.10 (GND), U5.7 (GND), U6.7 (GND), U7.8 (GND), U8.8 (GND), U8.15 (E), U9.8 (GND), U9.15 (E), U10.8 (GND), U10.15 (E), U11.3 (I1a), U11.8 (GND), U11.15 (E), U12.8 (GND), U13.1 (GND), U14.7 (GND), U15.7 (GND), U16.7 (GND), U17.1 (Vss), U17.21 (Vss), U18.1 (OEa)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
unnamed: J2.1, SW1.1, U35.15 (Q5)
unnamed: J2.3, R18.2, SW1.3, U1.13
unnamed: J2.5, SW2.1, U35.12 (Q4)
unnamed: J2.6, R1.1, R5.1, SW2.3, U1.9, U2.9, U2.39, U12.9 (A), U13.39 (TSC), U16.13, U50.2
unnamed: Q1.1 (B), R4.2
unnamed: Q2.1 (B), R5.2
unnamed: Q2.2 (C), R6.1
unnamed: Q3.2 (B), R6.2, R7.1
unnamed: Q3.1 (C), VR1.1 (IN)
unnamed: Q4.1 (B), R20.1, R21.1
unnamed: Q5.1 (B), R22.2
unnamed: R16.2, U15.6
unnamed: R17.2, U16.6
unnamed: U1.6, U34.4
unnamed: U1.10, U32.5
unnamed: U1.12, U34.13
unnamed: U2.4, U50.5
unnamed: U2.5, U31.8
unnamed: U2.6, U50.4
unnamed: U4.9 (Q1), U5.10
unnamed: U4.8 (Q2), U5.9
unnamed: FB2.2, U6.8 (CLK)
unnamed: U2.13, U6.4 (QB), U7.2 (I0a), U7.10 (I1c)
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
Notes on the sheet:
UNUSED UNITS
The CommonPET
R/~{W}
PURPLE
SuperPET Waterloo $A and $B (U47)
PRG
DECOUPLING
SuperPET Waterloo $C and $D (U48)
6502
SuperPET Waterloo $E and $F 50Hz (U49)
6809
was forgotton in first ASSY
R25 in later revisions, not on 324100
added in later versions located at place of FB2
bridged with factory bodge on ASSY 324100 removed in later revisions

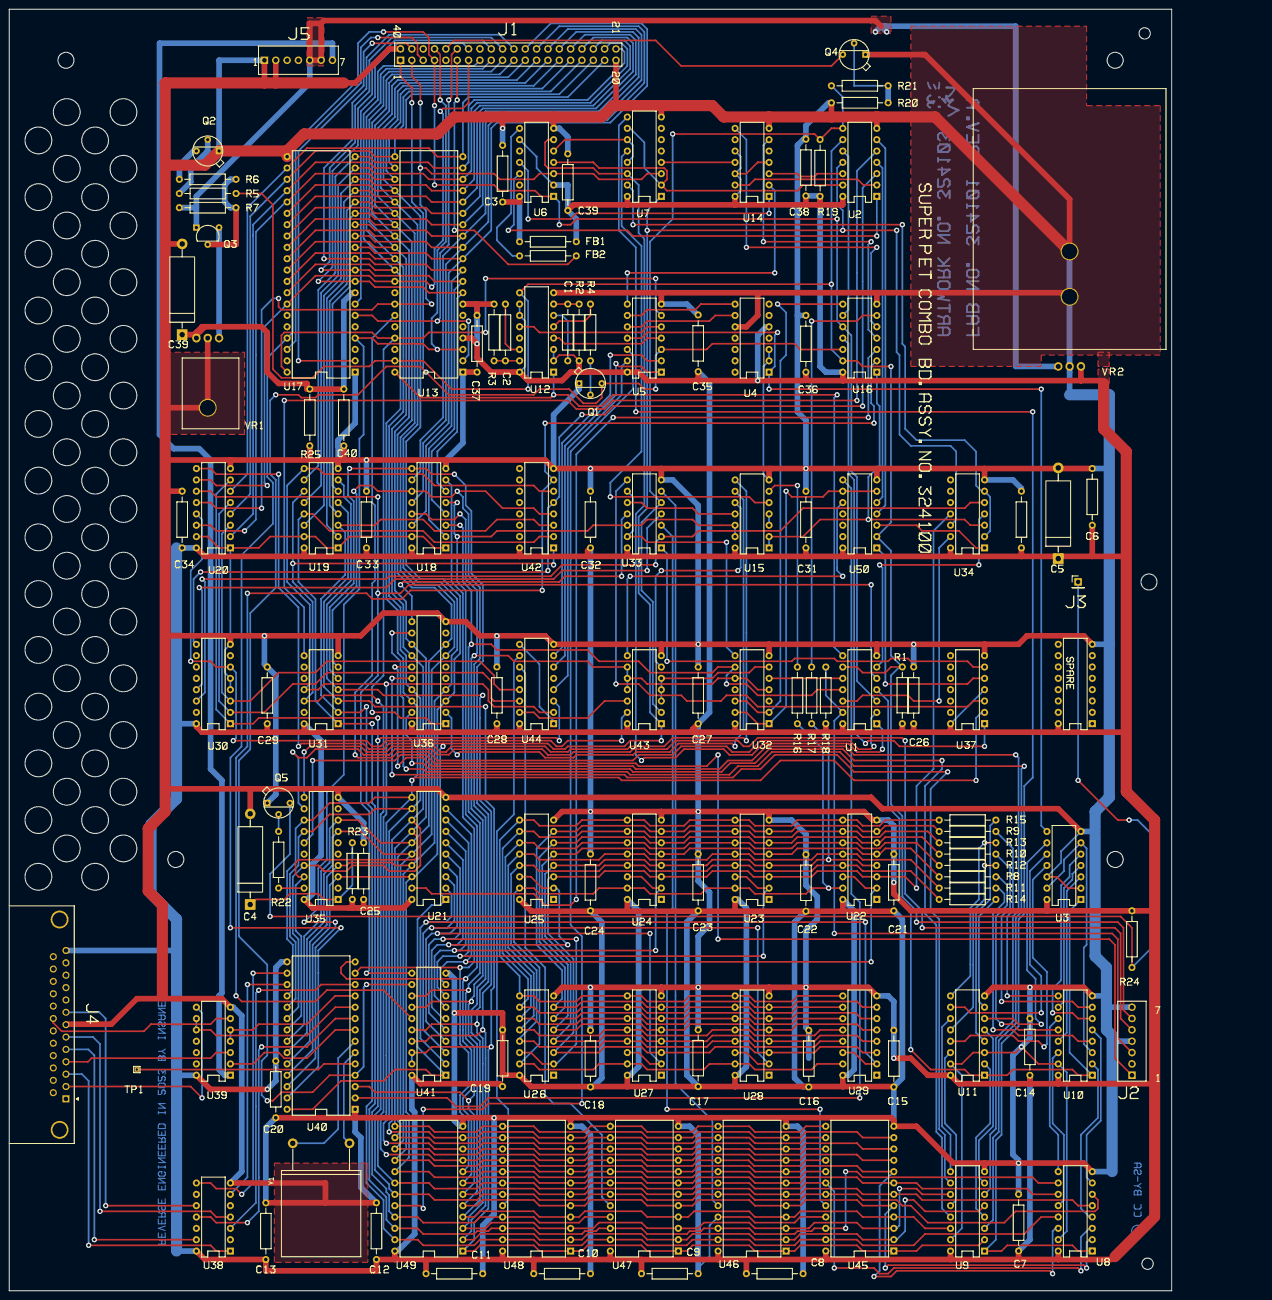
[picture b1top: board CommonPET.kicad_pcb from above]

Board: 2 copper layers, 280.7 x 287.0 mm, 133 parts (0 on the bottom side), 208 nets.

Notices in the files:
CommonPET.kicad_pcb:
License: CC BY-SA 4.0
